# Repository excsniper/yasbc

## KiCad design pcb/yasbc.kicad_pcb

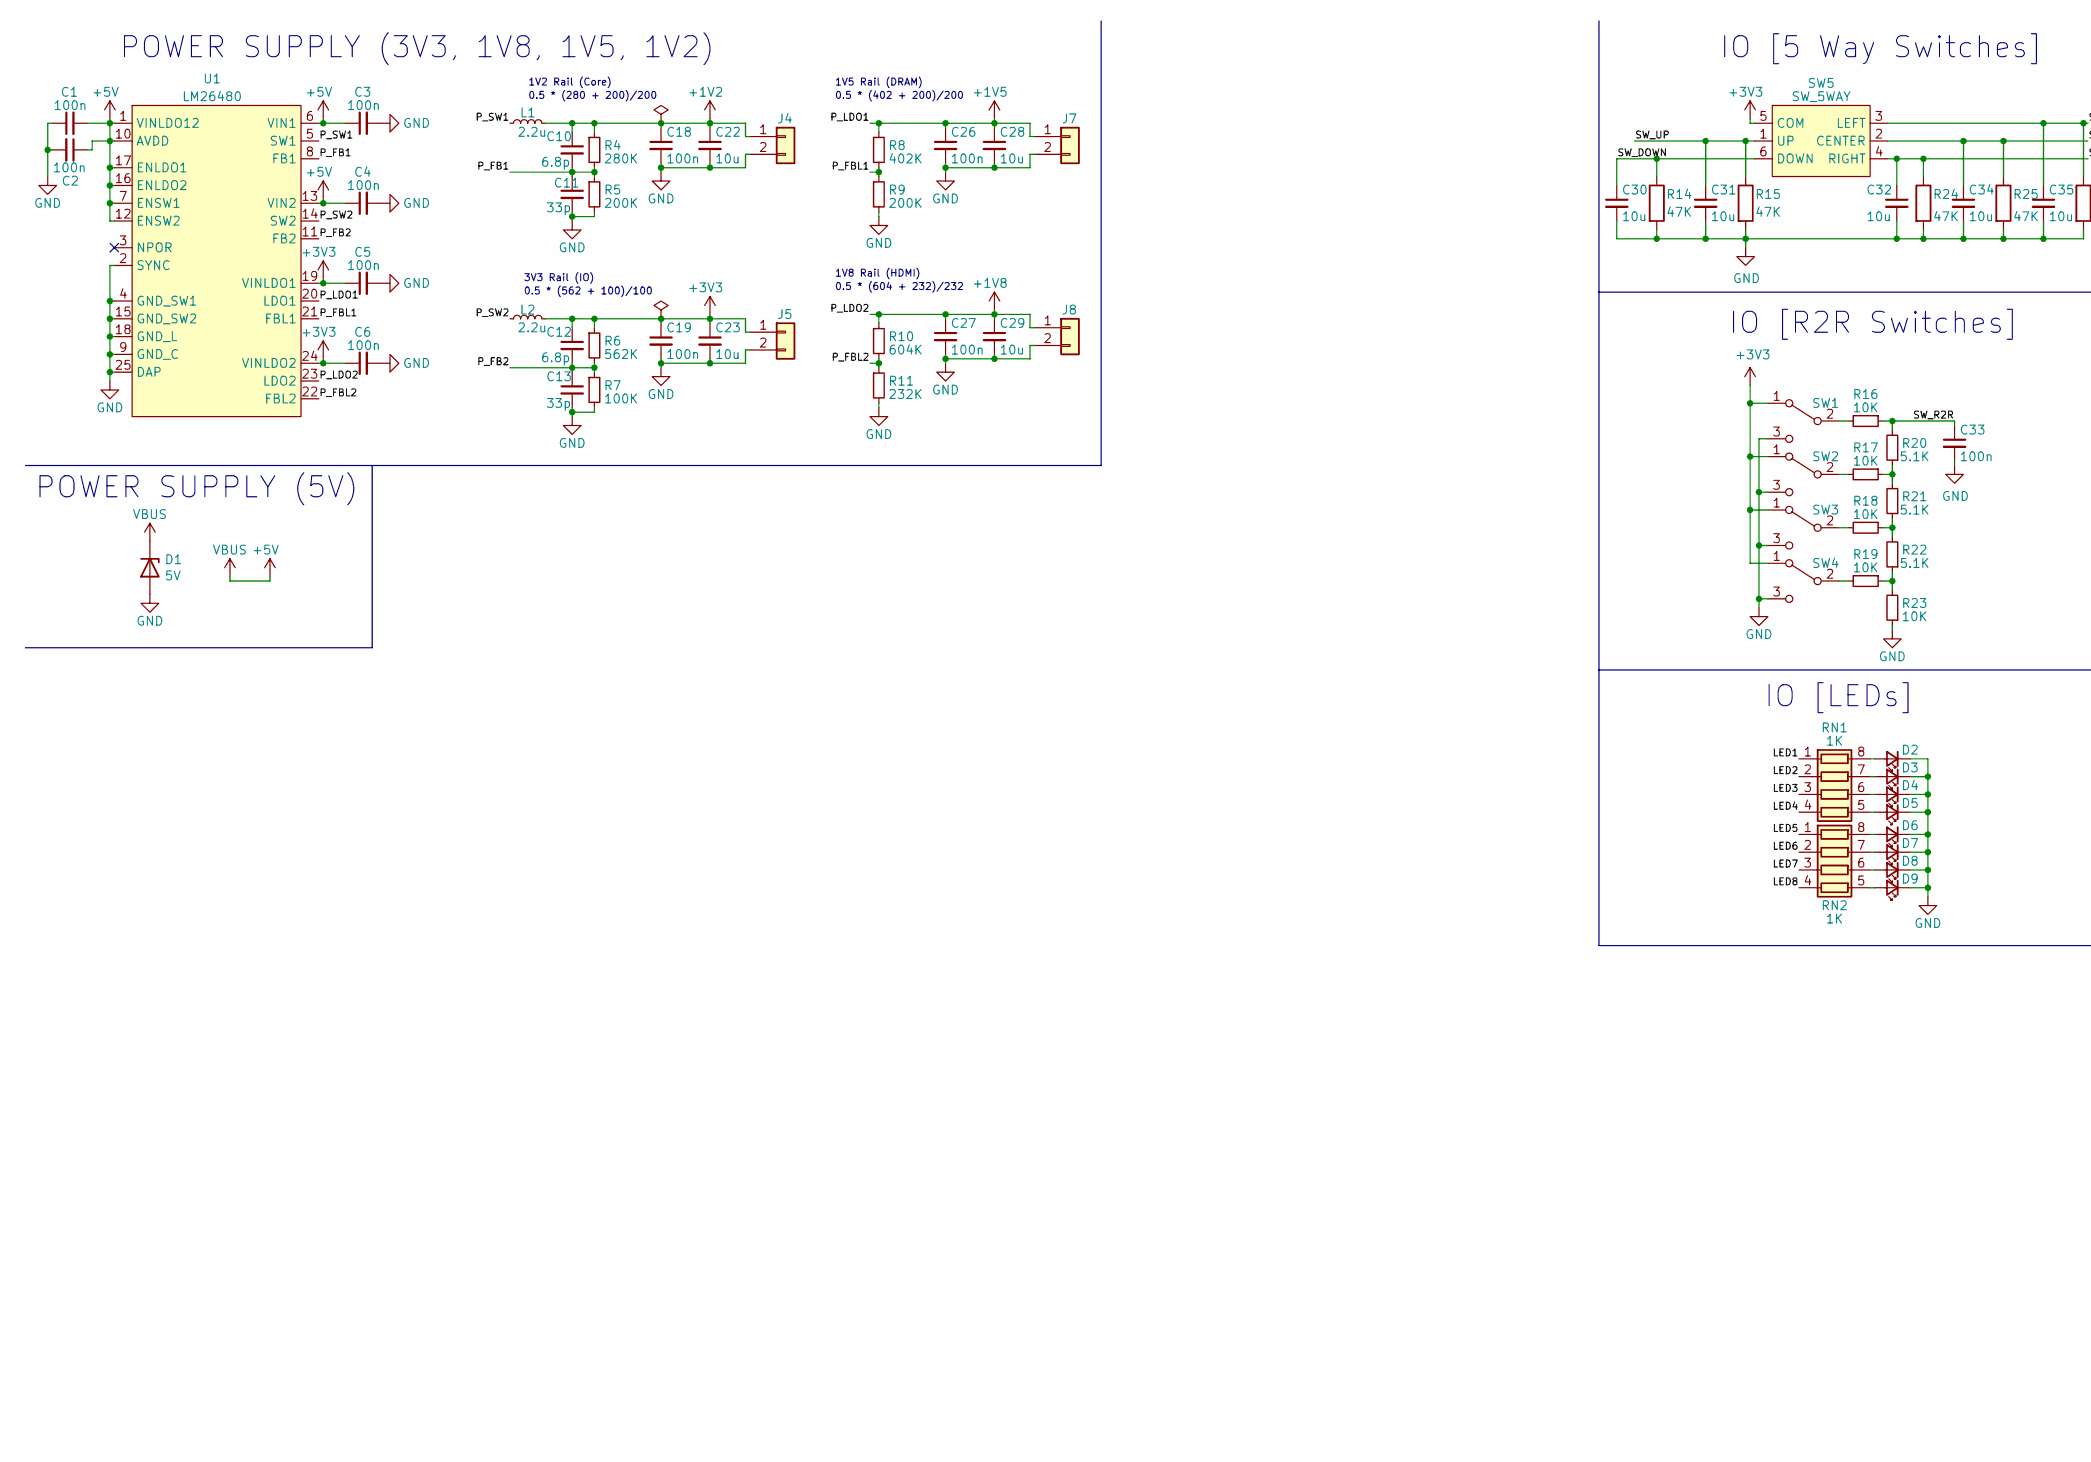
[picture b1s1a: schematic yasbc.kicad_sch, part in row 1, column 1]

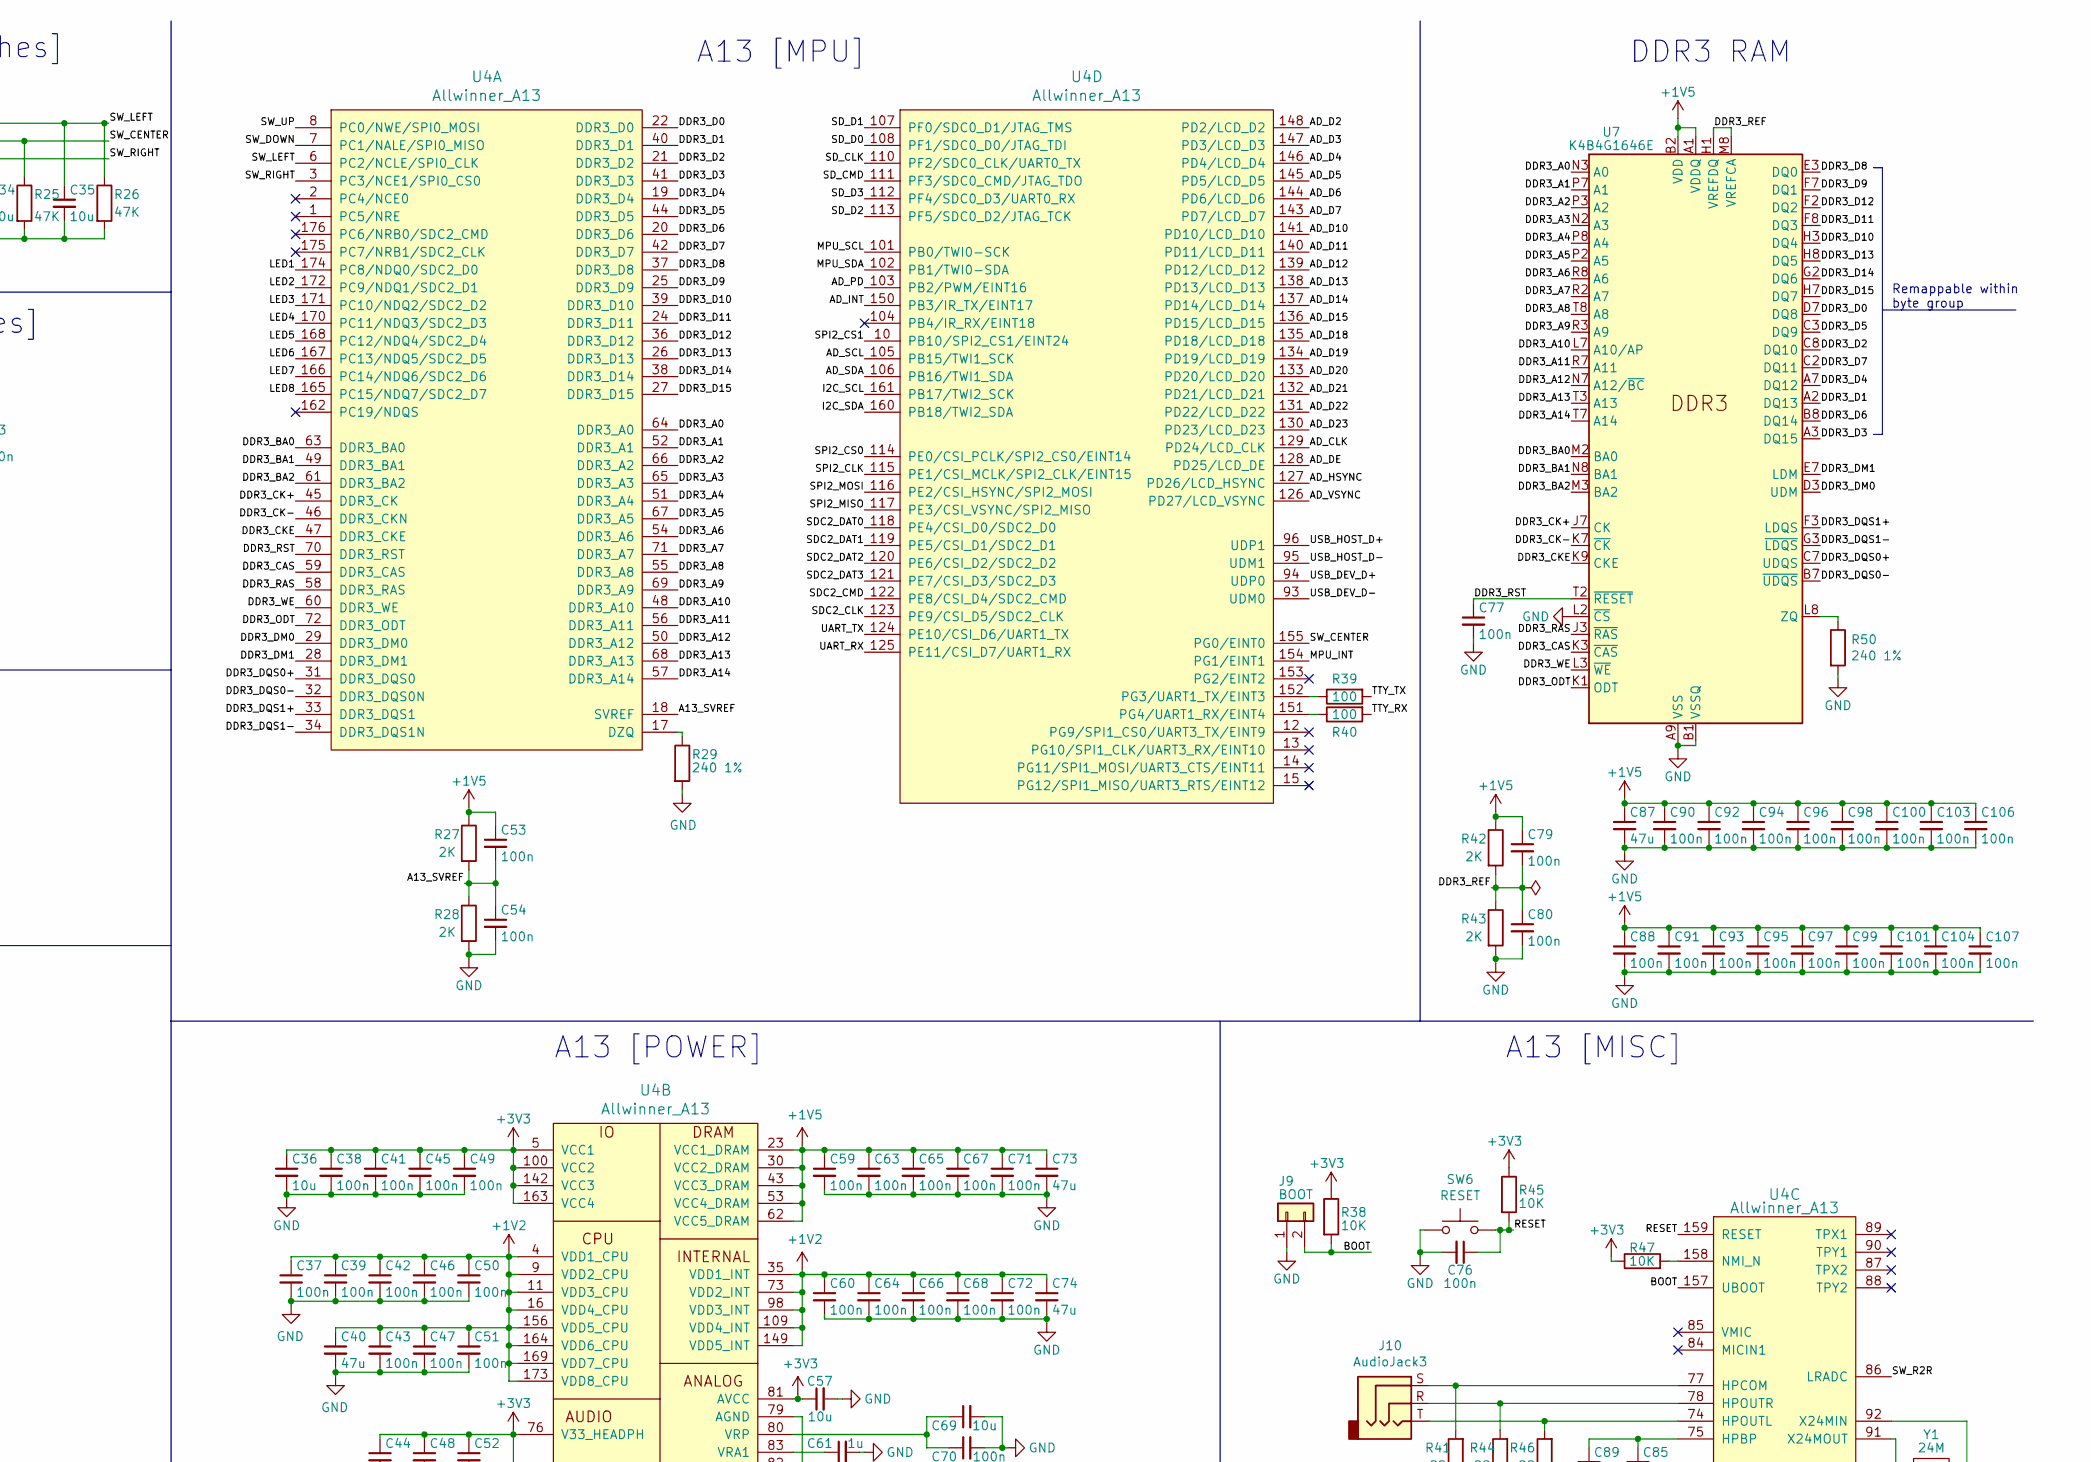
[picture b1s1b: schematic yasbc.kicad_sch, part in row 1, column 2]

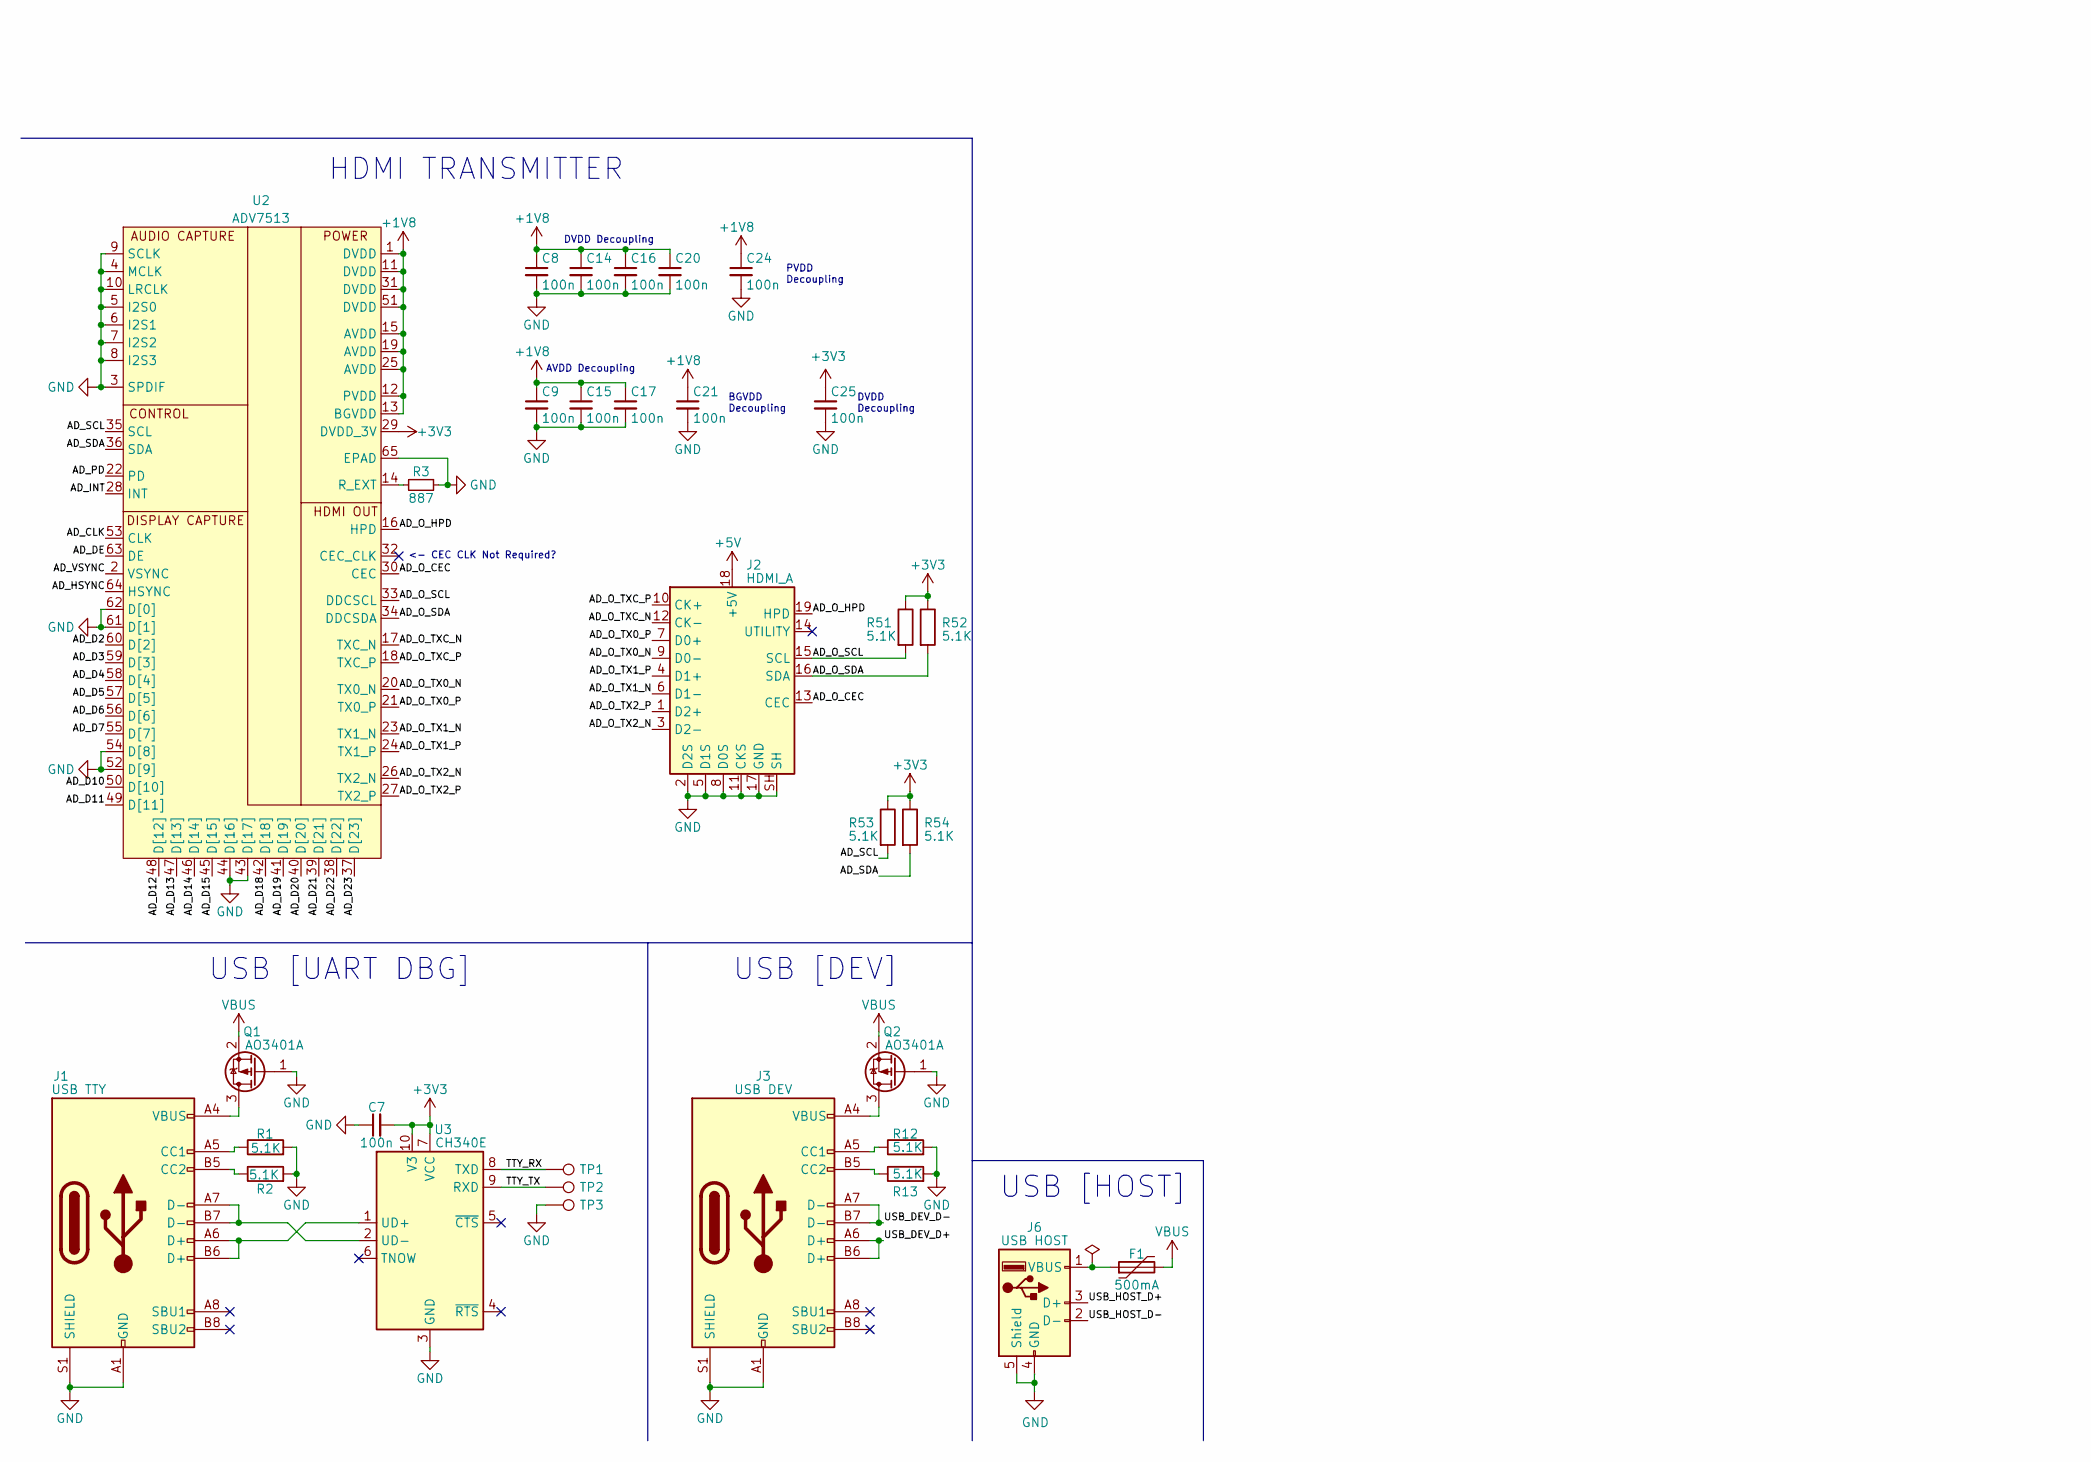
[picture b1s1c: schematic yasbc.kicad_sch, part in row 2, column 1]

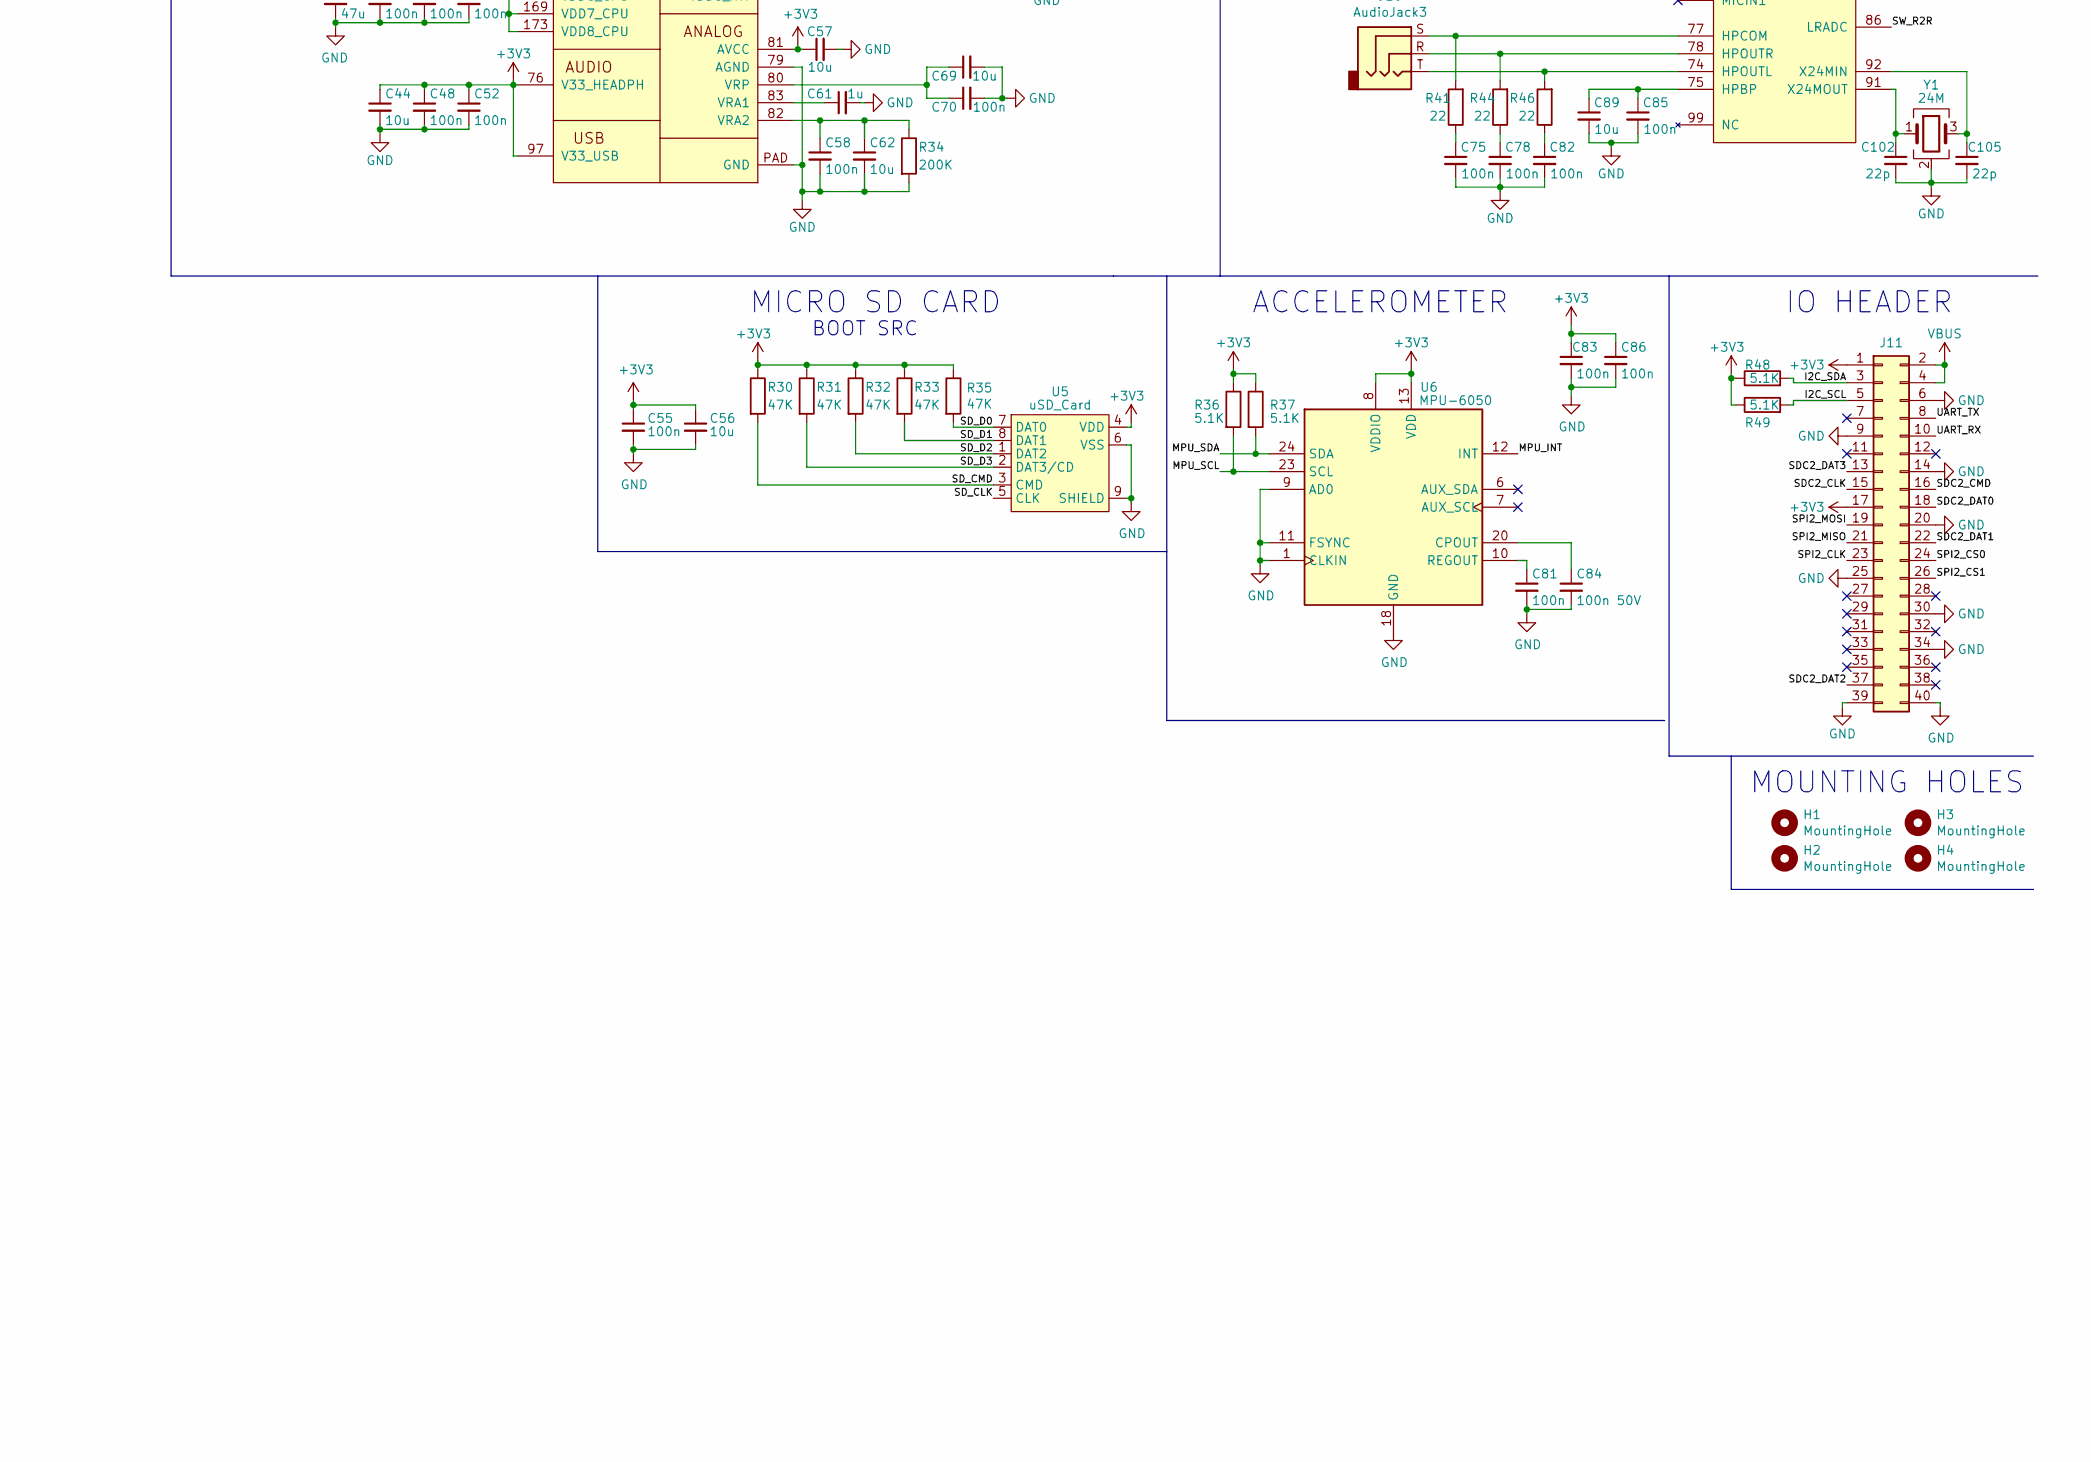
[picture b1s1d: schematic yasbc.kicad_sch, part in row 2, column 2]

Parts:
C1, C2, C3, C4, C5, C6, C7, C8, C9, C14, C15, C16, C17, C18, C19, C20, C21, C24, C25, C26, C27, C33, C37, C38, C39, C41, C42, C43, C45, C46, C47, C48, C49, C50, C51, C52, C53, C54, C55, C58, C59, C60, C63, C64, C65, C66, C67, C68, C70, C71, C72, C75, C76, C77, C78, C79, C80, C81, C82, C83, C85, C86, C88, C90, C91, C92, C93, C94, C95, C96, C97, C98, C99, C100, C101, C103, C104, C106, C107: 100n; C_0402_1005Metric
C10, C12: 6.8p; C_0402_1005Metric
C11, C13: 33p; C_0402_1005Metric
C22, C23, C28, C29, C30, C31, C32, C34, C35, C36, C44, C56, C57, C62, C69, C89: 10u; C_0402_1005Metric
C40, C73, C74, C87: 47u; C_0603_1608Metric
C61: 1u; C_0402_1005Metric
C84: 100n 50V; C_0402_1005Metric
C102, C105: 22p; C_0603_1608Metric
D1: 5V; D_SMB
D2, D3, D4, D5, D6, D7, D8, D9: LED_Small; LED_0603_1608Metric
F1: 500mA; Fuse_0805_2012Metric_Pad1.15x1.40mm_HandSolder
H1, H2, H3, H4: MountingHole; MountingHole_3.2mm_M3
J1: USB TTY; USB_C_Receptacle_HRO_TYPE-C-31-M-12
J2: HDMI_A; HDMI_A_Molex_208658-1001_Horizontal
J3: USB DEV; USB_C_Receptacle_HRO_TYPE-C-31-M-12
J4, J5, J7, J8: 1V5; PinHeader_1x02_P2.54mm_Vertical
J6: USB HOST; USB_A_CONNFLY_DS1095-WNR0
J9: BOOT; PinHeader_1x02_P2.54mm_Vertical
J10: AudioJack3; AudioJack
J11: Conn_02x20_Odd_Even; PinHeader_2x20_P2.54mm_Vertical
L1, L2: 2.2u; Inductor_5.2x5.8x4.5mm
Q1, Q2: AO3401A; SOT-23
R1, R2, R12, R13, R20, R21, R22, R36, R37, R48, R49, R51, R52, R53, R54: 5.1K; R_0603_1608Metric
R3: 887; R_0603_1608Metric
R4: 280K; R_0603_1608Metric
R5, R9, R34: 200K; R_0603_1608Metric
R6: 562K; R_0603_1608Metric
R7: 100K; R_0603_1608Metric
R8: 402K; R_0603_1608Metric
R10: 604K; R_0603_1608Metric
R11: 232K; R_0603_1608Metric
R14, R15, R24, R25, R26, R30, R31, R32, R33, R35: 47K; R_0603_1608Metric
R16, R17, R18, R19, R23, R38, R45, R47: 10K; R_0603_1608Metric
R27, R28, R42, R43: 2K; R_0603_1608Metric
R29, R50: 240 1%; R_0603_1608Metric
R39, R40: 100; R_0603_1608Metric
R41, R44, R46: 22; R_0603_1608Metric
RN1, RN2: 1K; R_Array_Convex_4x0603
SW1, SW2, SW3, SW4: SW_SPDT; SS-12D10
SW5: SW_5WAY; Switches_ALPS-SKRHAAE010
SW6: RESET; HYP-1TS002B-2500-4300-CT
TP1: TX; TestPoint_Pad_D2.0mm
TP2: RX; TestPoint_Pad_D2.0mm
TP3: GND; TestPoint_Pad_D2.0mm
U1: LM26480; WQFN-24-1EP_4x4mm_P0.5mm_EP2.6x2.6mm
U2: ADV7513; LQFP-64-1EP_10x10mm_P0.5mm_EP5x5mm
U3: CH340E; MSOP-10_3x3mm_P0.5mm
U4: Allwinner_A13; LQFP-176_20x20mm_P0.4mm_PAD
U5: uSD_Card; microSD
U6: MPU-6050; InvenSense_QFN-24_4x4mm_P0.5mm
U7: K4B4G1646E; BGA-96_9.0x13.0mm_Layout2x3x16_P0.8mm
Y1: 24M; Crystal_SMD_2016-4Pin_2.0x1.6mm

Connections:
+1V2: C10.1, C18.1, C22.1, C37.1, C39.1, C40.1, C42.1, C43.1, C46.1, C47.1, C50.1, C51.1, C60.1, C64.1, C66.1, C68.1, C72.1, C74.1, J4.1, L1.2, R4.1, U4.4 (VDD1_CPU), U4.9 (VDD2_CPU), U4.11 (VDD3_CPU), U4.16 (VDD4_CPU), U4.35 (VDD1_INT), U4.73 (VDD2_INT), U4.98 (VDD3_INT), U4.109 (VDD4_INT), U4.149 (VDD5_INT), U4.156 (VDD5_CPU), U4.164 (VDD6_CPU), U4.169 (VDD7_CPU), U4.173 (VDD8_CPU)
+1V5: C26.1, C28.1, C53.1, C59.1, C63.1, C65.1, C67.1, C71.1, C73.1, C79.1, C87.1, C88.1, C90.1, C91.1, C92.1, C93.1, C94.1, C95.1, C96.1, C97.1, C98.1, C99.1, C100.1, C101.1, C103.1, C104.1, C106.1, C107.1, J7.1, R8.1, R27.1, R42.1, U1.20 (LDO1), U4.23 (VCC1_DRAM), U4.30 (VCC2_DRAM), U4.43 (VCC3_DRAM), U4.53 (VCC4_DRAM), U4.62 (VCC5_DRAM), U7.A1 (VDDQ), U7.A8 (VDDQ), U7.B2 (VDD), U7.C1 (VDDQ), U7.C9 (VDDQ), U7.D2 (VDDQ), U7.D9 (VDD), U7.E9 (VDDQ), U7.F1 (VDDQ), U7.G7 (VDD), U7.H2 (VDDQ), U7.H9 (VDDQ), U7.K2 (VDD), U7.K8 (VDD), U7.N1 (VDD), U7.N9 (VDD), U7.R1 (VDD), U7.R9 (VDD)
+1V8: C8.1, C9.1, C14.1, C15.1, C16.1, C17.1, C20.1, C21.1, C24.1, C27.1, C29.1, J8.1, R10.1, U1.23 (LDO2), U2.1 (DVDD), U2.11 (DVDD), U2.12 (PVDD), U2.13 (BGVDD), U2.15 (AVDD), U2.19 (AVDD), U2.25 (AVDD), U2.31 (DVDD), U2.51 (DVDD)
+3V3: C5.1, C6.1, C7.2, C12.1, C19.1, C23.1, C25.1, C36.1, C38.1, C41.1, C44.1, C45.1, C48.1, C49.1, C52.1, C55.1, C56.1, C57.1, C83.1, C86.1, J5.1, J11.1, J11.17, L2.2, R6.1, R30.1, R31.1, R32.1, R33.1, R35.1, R36.1, R37.1, R38.1, R45.1, R47.1, R48.1, R49.1, R51.1, R52.1, R53.1, R54.1, SW1.1 (A), SW2.1 (A), SW3.1 (A), SW4.1 (A), SW5.5 (COM), U1.19 (VINLDO1), U1.24 (VINLDO2), U2.29 (DVDD_3V), U3.7 (VCC), U3.10 (V3), U4.5 (VCC1), U4.76 (V33_HEADPH), U4.81 (AVCC), U4.97 (V33_USB), U4.100 (VCC2), U4.142 (VCC3), U4.163 (VCC4), U5.4 (VDD), U6.8 (VDDIO), U6.13 (VDD)
+5V: C1.2, C2.1, C3.1, C4.1, D1.1 (K), F1.2, J2.18 (+5V), J11.2, J11.4, Q1.2 (S), Q2.2 (S), U1.1 (VINLDO12), U1.6 (VIN1), U1.7 (ENSW1), U1.10 (AVDD), U1.12 (ENSW2), U1.13 (VIN2), U1.16 (ENLDO2), U1.17 (ENLDO1)
/A13_SVREF: C53.2, C54.1, R27.2, R28.1, U4.18 (SVREF)
/AD_CLK: U2.53 (CLK), U4.129 (PD24/LCD_CLK)
/AD_D2: U2.60 (D[2]), U4.148 (PD2/LCD_D2)
/AD_D3: U2.59 (D[3]), U4.147 (PD3/LCD_D3)
/AD_D4: U2.58 (D[4]), U4.146 (PD4/LCD_D4)
/AD_D5: U2.57 (D[5]), U4.145 (PD5/LCD_D5)
/AD_D6: U2.56 (D[6]), U4.144 (PD6/LCD_D6)
/AD_D7: U2.55 (D[7]), U4.143 (PD7/LCD_D7)
/AD_D10: U2.50 (D[10]), U4.141 (PD10/LCD_D10)
/AD_D11: U2.49 (D[11]), U4.140 (PD11/LCD_D11)
/AD_D12: U2.48 (D[12]), U4.139 (PD12/LCD_D12)
/AD_D13: U2.47 (D[13]), U4.138 (PD13/LCD_D13)
/AD_D14: U2.46 (D[14]), U4.137 (PD14/LCD_D14)
/AD_D15: U2.45 (D[15]), U4.136 (PD15/LCD_D15)
/AD_D18: U2.42 (D[18]), U4.135 (PD18/LCD_D18)
/AD_D19: U2.41 (D[19]), U4.134 (PD19/LCD_D19)
/AD_D20: U2.40 (D[20]), U4.133 (PD20/LCD_D20)
/AD_D21: U2.39 (D[21]), U4.132 (PD21/LCD_D21)
/AD_D22: U2.38 (D[22]), U4.131 (PD22/LCD_D22)
/AD_D23: U2.37 (D[23]), U4.130 (PD23/LCD_D23)
/AD_DE: U2.63 (DE), U4.128 (PD25/LCD_DE)
/AD_HSYNC: U2.64 (HSYNC), U4.127 (PD26/LCD_HSYNC)
/AD_INT: U2.28 (INT), U4.150 (PB3/IR_TX/EINT17)
/AD_O_CEC: J2.13 (CEC), U2.30 (CEC)
/AD_O_HPD: J2.19 (HPD), U2.16 (HPD)
/AD_O_SCL: J2.15 (SCL), R51.2, U2.33 (DDCSCL)
/AD_O_SDA: J2.16 (SDA), R52.2, U2.34 (DDCSDA)
/AD_O_TX0_N: J2.9 (D0-), U2.20 (TX0_N)
/AD_O_TX0_P: J2.7 (D0+), U2.21 (TX0_P)
/AD_O_TX1_N: J2.6 (D1-), U2.23 (TX1_N)
/AD_O_TX1_P: J2.4 (D1+), U2.24 (TX1_P)
/AD_O_TX2_N: J2.3 (D2-), U2.26 (TX2_N)
/AD_O_TX2_P: J2.1 (D2+), U2.27 (TX2_P)
/AD_O_TXC_N: J2.12 (CK-), U2.17 (TXC_N)
/AD_O_TXC_P: J2.10 (CK+), U2.18 (TXC_P)
/AD_PD: U2.22 (PD), U4.103 (PB2/PWM/EINT16)
/AD_SCL: R53.2, U2.35 (SCL), U4.105 (PB15/TWI1_SCK)
/AD_SDA: R54.2, U2.36 (SDA), U4.106 (PB16/TWI1_SDA)
/AD_VSYNC: U2.2 (VSYNC), U4.126 (PD27/LCD_VSYNC)
/BOOT: J9.2, R38.2, U4.157 (UBOOT)
/DDR3_A0: U4.64 (DDR3_A0), U7.N3 (A0)
/DDR3_A1: U4.52 (DDR3_A1), U7.P7 (A1)
/DDR3_A2: U4.66 (DDR3_A2), U7.P3 (A2)
/DDR3_A3: U4.65 (DDR3_A3), U7.N2 (A3)
/DDR3_A4: U4.51 (DDR3_A4), U7.P8 (A4)
/DDR3_A5: U4.67 (DDR3_A5), U7.P2 (A5)
/DDR3_A6: U4.54 (DDR3_A6), U7.R8 (A6)
/DDR3_A7: U4.71 (DDR3_A7), U7.R2 (A7)
/DDR3_A8: U4.55 (DDR3_A8), U7.T8 (A8)
/DDR3_A9: U4.69 (DDR3_A9), U7.R3 (A9)
/DDR3_A10: U4.48 (DDR3_A10), U7.L7 (A10/AP)
/DDR3_A11: U4.56 (DDR3_A11), U7.R7 (A11)
/DDR3_A12: U4.50 (DDR3_A12), U7.N7 (A12/~BC)
/DDR3_A13: U4.68 (DDR3_A13), U7.T3 (A13)
/DDR3_A14: U4.57 (DDR3_A14), U7.T7 (A14)
/DDR3_BA0: U4.63 (DDR3_BA0), U7.M2 (BA0)
/DDR3_BA1: U4.49 (DDR3_BA1), U7.N8 (BA1)
/DDR3_BA2: U4.61 (DDR3_BA2), U7.M3 (BA2)
/DDR3_CAS: U4.59 (DDR3_CAS), U7.K3 (~CAS)
/DDR3_CK+: U4.45 (DDR3_CK), U7.J7 (CK)
/DDR3_CK-: U4.46 (DDR3_CKN), U7.K7 (~CK)
/DDR3_CKE: U4.47 (DDR3_CKE), U7.K9 (CKE)
/DDR3_D0: U4.22 (DDR3_D0), U7.D7 (DQ8)
/DDR3_D1: U4.40 (DDR3_D1), U7.A2 (DQ13)
/DDR3_D2: U4.21 (DDR3_D2), U7.C8 (DQ10)
/DDR3_D3: U4.41 (DDR3_D3), U7.A3 (DQ15)
/DDR3_D4: U4.19 (DDR3_D4), U7.A7 (DQ12)
/DDR3_D5: U4.44 (DDR3_D5), U7.C3 (DQ9)
/DDR3_D6: U4.20 (DDR3_D6), U7.B8 (DQ14)
/DDR3_D7: U4.42 (DDR3_D7), U7.C2 (DQ11)
/DDR3_D8: U4.37 (DDR3_D8), U7.E3 (DQ0)
/DDR3_D9: U4.25 (DDR3_D9), U7.F7 (DQ1)
/DDR3_D10: U4.39 (DDR3_D10), U7.H3 (DQ4)
/DDR3_D11: U4.24 (DDR3_D11), U7.F8 (DQ3)
/DDR3_D12: U4.36 (DDR3_D12), U7.F2 (DQ2)
/DDR3_D13: U4.26 (DDR3_D13), U7.H8 (DQ5)
/DDR3_D14: U4.38 (DDR3_D14), U7.G2 (DQ6)
/DDR3_D15: U4.27 (DDR3_D15), U7.H7 (DQ7)
/DDR3_DM0: U4.29 (DDR3_DM0), U7.D3 (UDM)
/DDR3_DM1: U4.28 (DDR3_DM1), U7.E7 (LDM)
/DDR3_DQS0+: U4.31 (DDR3_DQS0), U7.C7 (UDQS)
/DDR3_DQS0-: U4.32 (DDR3_DQS0N), U7.B7 (~UDQS)
/DDR3_DQS1+: U4.33 (DDR3_DQS1), U7.F3 (LDQS)
/DDR3_DQS1-: U4.34 (DDR3_DQS1N), U7.G3 (~LDQS)
/DDR3_ODT: U4.72 (DDR3_ODT), U7.K1 (ODT)
/DDR3_RAS: U4.58 (DDR3_RAS), U7.J3 (~RAS)
/DDR3_REF: C79.2, C80.1, R42.2, R43.1, U7.H1 (VREFDQ), U7.M8 (VREFCA)
/DDR3_RST: C77.1, U4.70 (DDR3_RST), U7.T2 (~RESET)
/DDR3_WE: U4.60 (DDR3_WE), U7.L3 (~WE)
/I2C_SCL: J11.5, R49.2, U4.161 (PB17/TWI2_SCK)
/I2C_SDA: J11.3, R48.2, U4.160 (PB18/TWI2_SDA)
/LED1: RN1.1 (R1.1), U4.174 (PC8/NDQ0/SDC2_D0)
/LED2: RN1.2 (R2.1), U4.172 (PC9/NDQ1/SDC2_D1)
/LED3: RN1.3 (R3.1), U4.171 (PC10/NDQ2/SDC2_D2)
/LED4: RN1.4 (R4.1), U4.170 (PC11/NDQ3/SDC2_D3)
/LED5: RN2.1 (R1.1), U4.168 (PC12/NDQ4/SDC2_D4)
/LED6: RN2.2 (R2.1), U4.167 (PC13/NDQ5/SDC2_D5)
/LED7: RN2.3 (R3.1), U4.166 (PC14/NDQ6/SDC2_D6)
/LED8: RN2.4 (R4.1), U4.165 (PC15/NDQ7/SDC2_D7)
/MPU_INT: U4.154 (PG1/EINT1), U6.12 (INT)
/MPU_SCL: R36.2, U4.101 (PB0/TWI0-SCK), U6.23 (SCL)
/MPU_SDA: R37.2, U4.102 (PB1/TWI0-SDA), U6.24 (SDA)
/P_FB1: C10.2, C11.1, R4.2, R5.1, U1.8 (FB1)
/P_FB2: C12.2, C13.1, R6.2, R7.1, U1.11 (FB2)
/P_FBL1: R8.2, R9.1, U1.21 (FBL1)
/P_FBL2: R10.2, R11.1, U1.22 (FBL2)
/P_SW1: L1.1, U1.5 (SW1)
/P_SW2: L2.1, U1.14 (SW2)
/RESET: C76.1, R45.2, SW6.2, U4.159 (RESET)
/SDC2_CLK: J11.15, U4.123 (PE9/CSI_D5/SDC2_CLK)
/SDC2_CMD: J11.16, U4.122 (PE8/CSI_D4/SDC2_CMD)
/SDC2_DAT0: J11.18, U4.118 (PE4/CSI_D0/SDC2_D0)
/SDC2_DAT1: J11.22, U4.119 (PE5/CSI_D1/SDC2_D1)
/SDC2_DAT2: J11.37, U4.120 (PE6/CSI_D2/SDC2_D2)
/SDC2_DAT3: J11.13, U4.121 (PE7/CSI_D3/SDC2_D3)
/SD_CLK: U4.110 (PF2/SDC0_CLK/UART0_TX), U5.5 (CLK)
/SD_CMD: R30.2, U4.111 (PF3/SDC0_CMD/JTAG_TDO), U5.3 (CMD)
/SD_D0: R35.2, U4.108 (PF1/SDC0_D0/JTAG_TDI), U5.7 (DAT0)
/SD_D1: R33.2, U4.107 (PF0/SDC0_D1/JTAG_TMS), U5.8 (DAT1)
/SD_D2: R32.2, U4.113 (PF5/SDC0_D2/JTAG_TCK), U5.1 (DAT2)
/SD_D3: R31.2, U4.112 (PF4/SDC0_D3/UART0_RX), U5.2 (DAT3/CD)
/SPI2_CLK: J11.23, U4.115 (PE1/CSI_MCLK/SPI2_CLK/EINT15)
/SPI2_CS0: J11.24, U4.114 (PE0/CSI_PCLK/SPI2_CS0/EINT14)
/SPI2_CS1: J11.26, U4.10 (PB10/SPI2_CS1/EINT24)
/SPI2_MISO: J11.21, U4.117 (PE3/CSI_VSYNC/SPI2_MISO)
/SPI2_MOSI: J11.19, U4.116 (PE2/CSI_HSYNC/SPI2_MOSI)
/SW_CENTER: C34.1, R25.1, SW5.2 (CENTER), U4.155 (PG0/EINT0)
/SW_DOWN: C30.1, R14.1, SW5.6 (DOWN), U4.7 (PC1/NALE/SPI0_MISO)
/SW_LEFT: C35.1, R26.1, SW5.3 (LEFT), U4.6 (PC2/NCLE/SPI0_CLK)
/SW_R2R: C33.1, R16.1, R20.2, U4.86 (LRADC)
/SW_RIGHT: C32.1, R24.1, SW5.4 (RIGHT), U4.3 (PC3/NCE1/SPI0_CS0)
/SW_UP: C31.1, R15.1, SW5.1 (UP), U4.8 (PC0/NWE/SPI0_MOSI)
/TTY_RX: R40.2, TP1.1, U3.8 (TXD)
/TTY_TX: R39.2, TP2.1, U3.9 (RXD)
/UART_RX: J11.10, U4.125 (PE11/CSI_D7/UART1_RX)
/UART_TX: J11.8, U4.124 (PE10/CSI_D6/UART1_TX)
/USB_DEV_D+: J3.A6 (D+), J3.B6 (D+), U4.94 (UDP0)
/USB_DEV_D-: J3.A7 (D-), J3.B7 (D-), U4.93 (UDM0)
/USB_HOST_D+: J6.3 (D+), U4.96 (UDP1)
/USB_HOST_D-: J6.2 (D-), U4.95 (UDM1)
GND: C1.1, C2.2, C3.2, C4.2, C5.2, C6.2, C7.1, C8.2, C9.2, C11.2, C13.2, C14.2, C15.2, C16.2, C17.2, C18.2, C19.2, C20.2, C21.2, C22.2, C23.2, C24.2, C25.2, C26.2, C27.2, C28.2, C29.2, C30.2, C31.2, C32.2, C33.2, C34.2, C35.2, C36.2, C37.2, C38.2, C39.2, C40.2, C41.2, C42.2, C43.2, C44.2, C45.2, C46.2, C47.2, C48.2, C49.2, C50.2, C51.2, C52.2, C54.2, C55.2, C56.2, C57.2, C58.2, C59.2, C60.2, C61.2, C62.2, C63.2, C64.2, C65.2, C66.2, C67.2, C68.2, C69.2, C70.2, C71.2, C72.2, C73.2, C74.2, C75.2, C76.2, C77.2, C78.2, C80.2, C81.2, C82.2, C83.2, C84.2, C85.2, C86.2, C87.2, C88.2, C89.2, C90.2, C91.2, C92.2, C93.2, C94.2, C95.2, C96.2, C97.2, C98.2, C99.2, C100.2, C101.2, C102.2, C103.2, C104.2, C105.2, C106.2, C107.2, D1.2 (A), D2.1 (K), D3.1 (K), D4.1 (K), D5.1 (K), D6.1 (K), D7.1 (K), D8.1 (K), D9.1 (K), J1.A1 (GND), J1.A12 (GND), J1.B1 (GND), J1.B12 (GND), J1.S1 (SHIELD), J2.2 (D2S), J2.5 (D1S), J2.8 (D0S), J2.11 (CKS), J2.17 (GND), J2.SH, J3.A1 (GND), J3.A12 (GND), J3.B1 (GND), J3.B12 (GND), J3.S1 (SHIELD), J4.2, J5.2, J6.4 (GND), J6.5 (Shield), J7.2, J8.2, J9.1, J11.6, J11.9, J11.14, J11.20, J11.25, J11.30, J11.34, J11.39, J11.40, Q1.1 (G), Q2.1 (G), R1.2, R2.2, R3.1, R5.2, R7.2, R9.2, R11.2, R12.2, R13.2, R14.2, R15.2, R23.1, R24.2, R25.2, R26.2, R28.2, R29.2, R34.2, R43.2, R50.2, SW1.3 (C), SW2.3 (C), SW3.3 (C), SW4.3 (C), SW6.1, TP3.1, U1.2 (SYNC)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
unnamed: C75.1, R41.1
unnamed: C78.1, R44.1
unnamed: C82.1, R46.1
unnamed: D2.2 (A), RN1.8 (R1.2)
unnamed: D3.2 (A), RN1.7 (R2.2)
unnamed: D4.2 (A), RN1.6 (R3.2)
unnamed: D5.2 (A), RN1.5 (R4.2)
unnamed: D6.2 (A), RN2.8 (R1.2)
unnamed: D7.2 (A), RN2.7 (R2.2)
unnamed: D8.2 (A), RN2.6 (R3.2)
unnamed: D9.2 (A), RN2.5 (R4.2)
unnamed: J1.A5 (CC1), R1.1
unnamed: J1.B5 (CC2), R2.1
unnamed: J3.A5 (CC1), R12.1
unnamed: J3.B5 (CC2), R13.1
unnamed: F1.1, J6.1 (VBUS)
unnamed: J1.A4 (VBUS), J1.A9 (VBUS), J1.B4 (VBUS), J1.B9 (VBUS), Q1.3 (D)
unnamed: J3.A4 (VBUS), J3.A9 (VBUS), J3.B4 (VBUS), J3.B9 (VBUS), Q2.3 (D)
unnamed: R17.1, R20.1, R21.2
unnamed: R18.1, R21.1, R22.2
unnamed: R19.1, R22.1, R23.2
unnamed: R16.2, SW1.2 (B)
unnamed: R17.2, SW2.2 (B)
unnamed: R18.2, SW3.2 (B)
unnamed: R19.2, SW4.2 (B)
unnamed: R3.2, U2.14 (R_EXT)
unnamed: J1.A6 (D+), J1.B6 (D+), U3.1 (UD+)
unnamed: J1.A7 (D-), J1.B7 (D-), U3.2 (UD-)
unnamed: R29.1, U4.17 (DZQ)
unnamed: C61.1, U4.83 (VRA1)
unnamed: C58.1, C62.1, R34.1, U4.82 (VRA2)
unnamed: C69.1, C70.1, U4.80 (VRP)
unnamed: C85.1, C89.1, U4.75 (HPBP)
unnamed: J10.S, R41.2, U4.77 (HPCOM)
unnamed: J10.T, R46.2, U4.74 (HPOUTL)
unnamed: J10.R, R44.2, U4.78 (HPOUTR)
unnamed: R47.2, U4.158 (NMI_N)
unnamed: C105.1, U4.92 (X24MIN), Y1.3
unnamed: C102.1, U4.91 (X24MOUT), Y1.1
unnamed: R39.1, U4.152 (PG3/UART1_TX/EINT3)
unnamed: R40.1, U4.151 (PG4/UART1_RX/EINT4)
unnamed: C84.1, U6.20 (CPOUT)
unnamed: C81.1, U6.10 (REGOUT)
unnamed: R50.1, U7.L8 (ZQ)

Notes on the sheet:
A13 [MISC]
USB [HOST]
IO [R2R Switches]
1V5 Rail (DRAM)
DVDD Decoupling
Remappable within byte group
POWER SUPPLY (3V3, 1V8, 1V5, 1V2)
IO [5 Way Switches]
0.5 * (280 + 200)/200
MOUNTING HOLES
0.5 * (604 + 232)/232
USB [UART DBG]
0.5 * (402 + 200)/200
0.5 * (562 + 100)/100
IO [LEDs]
BGVDD Decoupling
PVDD Decoupling
IO HEADER
1V8 Rail (HDMI)
POWER SUPPLY (5V)
<- CEC CLK Not Required?
3V3 Rail (IO)
1V2 Rail (Core)
DDR3 RAM
USB [DEV]
A13 [POWER]
DVDD Decoupling
HDMI TRANSMITTER
A13 [MPU]
AVDD Decoupling
ACCELEROMETER
BOOT SRC
MICRO SD CARD

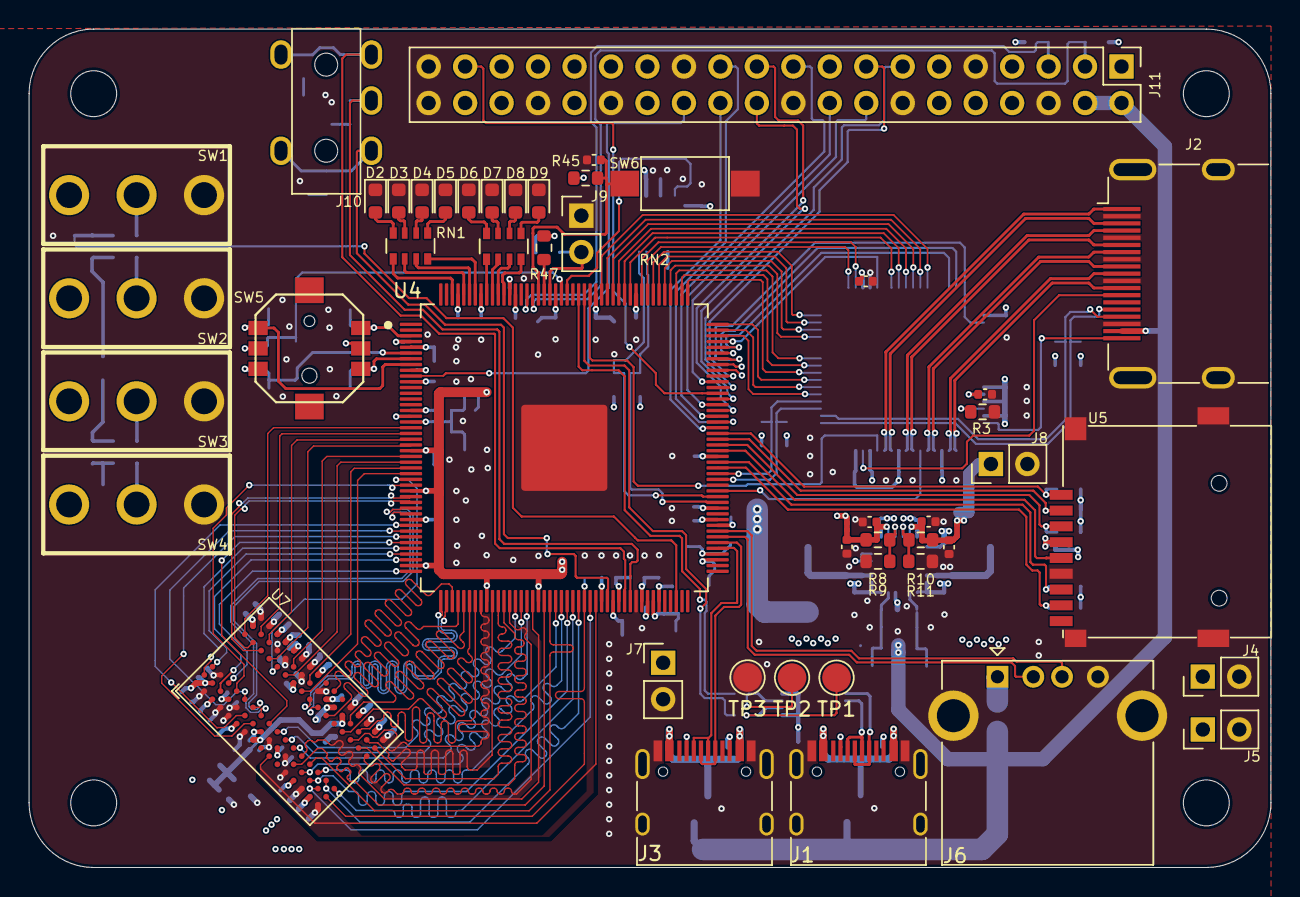
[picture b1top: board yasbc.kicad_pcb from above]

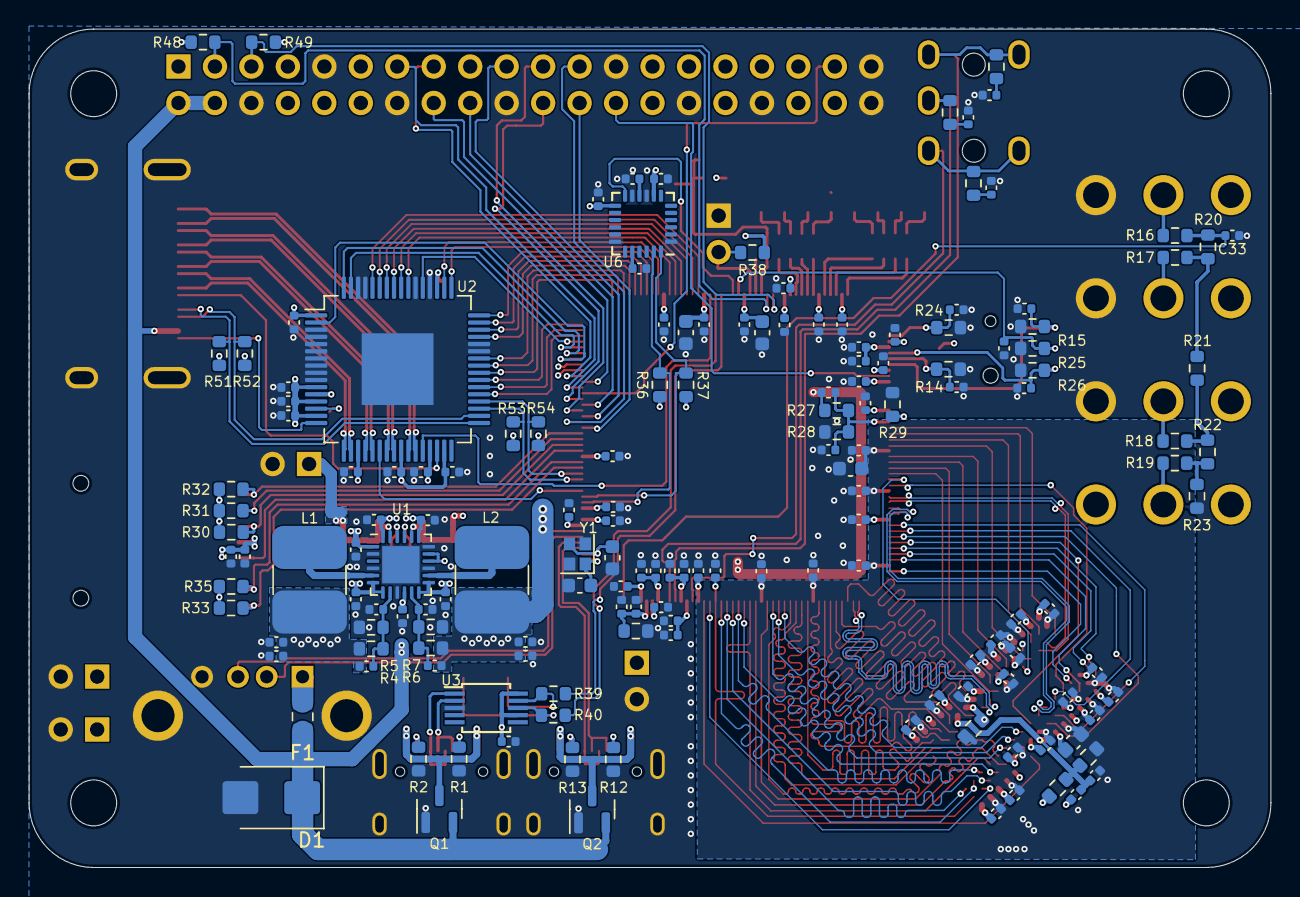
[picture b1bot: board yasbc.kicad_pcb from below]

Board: 4 copper layers, 86.5 x 58.4 mm, 209 parts (158 on the bottom side), 190 nets.
